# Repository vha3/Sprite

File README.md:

# Compressed Sprite

This board is schematically identical to the one in the master branch, but uses smaller surface-mount components to reduce the board footprint from 3.5x3.5 cm to 3x3 cm. The users' manual from the master branch applies to this board as well.

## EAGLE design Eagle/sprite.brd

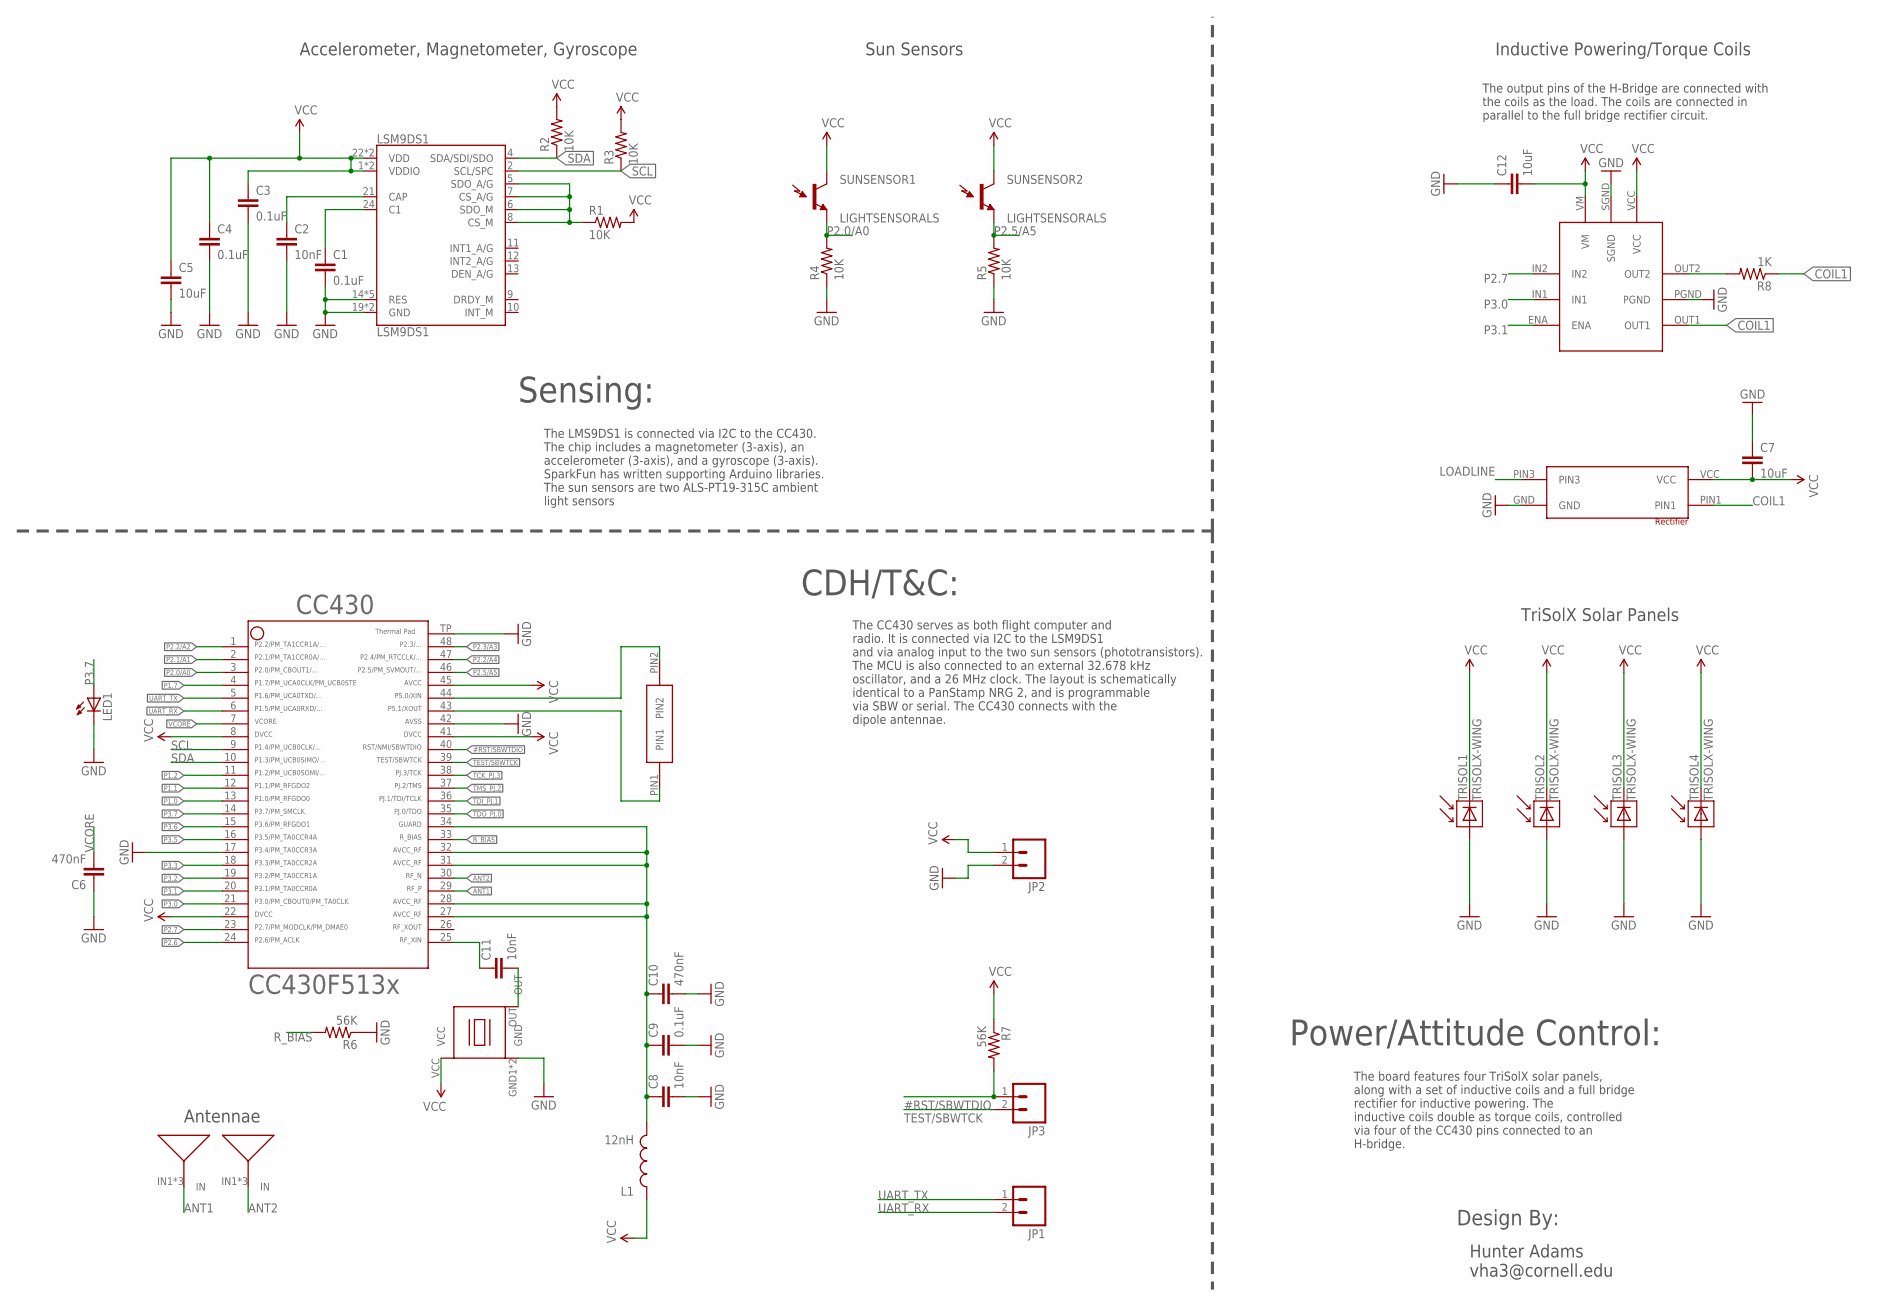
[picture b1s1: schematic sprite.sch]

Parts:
32KHZ: SPRITECRYSTALSPRITECRYSTAL; SPRITECRYSTAL
ANTENNA1, ANTENNA2: ANTENNA
C1, C3, C4, C9: 0.1uF; 0402-CAP
C2, C8, C11: 10nF; 0402-CAP
C5, C7, C12: 10uF; 0402-CAP
C6, C10: 470nF; 0402-CAP
CC430: CC430F513X---RGZ48; RGZ48
H-BRIDGE: LV8417CS
JP1, JP2, JP3: M02PTH; 1X02
L1: 12nH; C0402
LED1: LED0603; LED-0603
LSM9DS1: LSM9DS1; LGA24-8X4
R1, R2, R3, R4, R5: 10K; 0402-RES
R6, R7: 56K; 0402-RES
R8: 1K; 0402-RES
RECTIFIER: NSR1030QMUTAG
SUNSENSOR1, SUNSENSOR2: LIGHTSENSORALS; ALS-PT19
TRISOL1, TRISOL2, TRISOL3, TRISOL4: TRISOLX-WING; TRISOLX-T01
TXCO: TCXO_7Z; TXC_7Z

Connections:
#RST/SBWTDIO: CC430.40, JP3.1, R7.2
ANT1: ANTENNA1.IN1, ANTENNA1.IN2, ANTENNA1.IN3, CC430.29
ANT2: ANTENNA2.IN1, ANTENNA2.IN2, ANTENNA2.IN3, CC430.30
COIL1: H-BRIDGE.OUT1, R8.1, RECTIFIER.PIN1
GND: C1.2, C2.2, C3.2, C4.2, C5.2, C6.1, C7.1, C8.2, C9.2, C10.2, C12.1, CC430.17, CC430.42, CC430.TP (49), H-BRIDGE.PGND, H-BRIDGE.SGND, JP2.2, LED1.C, LSM9DS1.14 (RES), LSM9DS1.15 (RES), LSM9DS1.16 (RES), LSM9DS1.17 (RES), LSM9DS1.18 (RES), LSM9DS1.19 (GND), LSM9DS1.20 (GND), R4.1, R5.1, R6.1, RECTIFIER.GND, TRISOL1.P$3 (A), TRISOL2.P$3 (A), TRISOL3.P$3 (A), TRISOL4.P$3 (A), TXCO.GND1 (GND), TXCO.GND2 (GND)
GUARD: C8.1, C9.1, C10.1, CC430.27, CC430.28, CC430.31, CC430.32, CC430.34, L1.2
LOADLINE: H-BRIDGE.OUT2, R8.2, RECTIFIER.PIN3
unnamed: C1.1, LSM9DS1.24 (C1)
unnamed: C2.1, LSM9DS1.21 (CAP)
unnamed: LSM9DS1.5 (SDO_A/G), LSM9DS1.6 (SDO_M), LSM9DS1.7 (CS_A/G), LSM9DS1.8 (CS_M), R1.1
unnamed: C11.1, CC430.25
unnamed: C11.2, TXCO.OUT
unnamed: 32KHZ.PIN2, CC430.44
unnamed: 32KHZ.PIN1, CC430.43
P1.0: CC430.13
P1.1: CC430.12
P1.2: CC430.11
P1.7: CC430.4
P2.0/A0: CC430.3, R4.2, SUNSENSOR1.E (E1)
P2.1/A1: CC430.2
P2.2/A2: CC430.1
P2.2/A4: CC430.47
P2.3/A3: CC430.48
P2.5/A5: CC430.46, R5.2, SUNSENSOR2.E (E1)
P2.6: CC430.24
P2.7: CC430.23, H-BRIDGE.IN2
P3.0: CC430.21, H-BRIDGE.IN1
P3.1: CC430.20, H-BRIDGE.ENA
P3.2: CC430.19
P3.3: CC430.18
P3.5: CC430.16
P3.6: CC430.15
P3.7: CC430.14, LED1.A
R_BIAS: CC430.33, R6.2
SCL: CC430.9, LSM9DS1.2 (SCL/SPC), R3.1
SDA: CC430.10, LSM9DS1.4 (SDA/SDI/SDO), R2.1
TCK_PJ.3: CC430.38
TDI_PJ.1: CC430.36
TDO_PJ.0: CC430.35
TEST/SBWTCK: CC430.39, JP3.2
TMS_PJ.2: CC430.37
UART_RX: CC430.6, JP1.2
UART_TX: CC430.5, JP1.1
VCC: C3.1, C4.1, C5.1, C7.2, C12.2, CC430.8, CC430.22, CC430.41, CC430.45, H-BRIDGE.VCC, H-BRIDGE.VM, JP2.1, L1.1, LSM9DS1.1 (VDDIO), LSM9DS1.3 (VDDIO), LSM9DS1.22 (VDD), LSM9DS1.23 (VDD), R1.2, R2.2, R3.2, R7.1, RECTIFIER.VCC, SUNSENSOR1.C (C1), SUNSENSOR2.C (C1), TRISOL1.P$2 (C), TRISOL2.P$2 (C), TRISOL3.P$2 (C), TRISOL4.P$2 (C), TXCO.VCC
VCORE: C6.2, CC430.7

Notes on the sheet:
Accelerometer, Magnetometer, Gyroscope
Sun Sensors
The LMS9DS1 is connected via I2C to the CC430. The chip includes a magnetometer (3-axis), an accelerometer (3-axis), and a gyroscope (3-axis). SparkFun has written supporting Arduino libraries. The sun sensors are two ALS-PT19-315C ambient light sensors
Sensing:
CDH/T&C:
The CC430 serves as both flight computer and radio. It is connected via I2C to the LSM9DS1 and via analog input to the two sun sensors (phototransistors). The MCU is also connected to an external 32.678 kHz oscillator, and a 26 MHz clock. The layout is schematically identical to a PanStamp NRG 2, a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
Power/Attitude Control:
The board features four TriSolX solar panels, along with a set of inductive coils and a full bridge rectifier for inductive powering. The inductive coils double as torque coils, controlled via four of the CC430 pins connected to an H-bridge.
Antennae
TriSolX Solar Panels
Inductive Powering/Torque Coils
Hunter Adams vha3@cornell.edu
Design By:
The output pins of the H-Bridge are connected with the coils as the load. The coils are connected in parallel to the full bridge rectifier circuit.

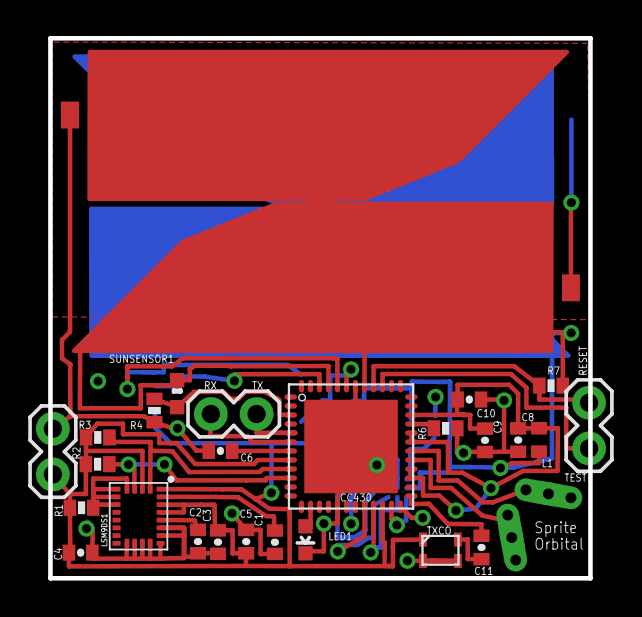
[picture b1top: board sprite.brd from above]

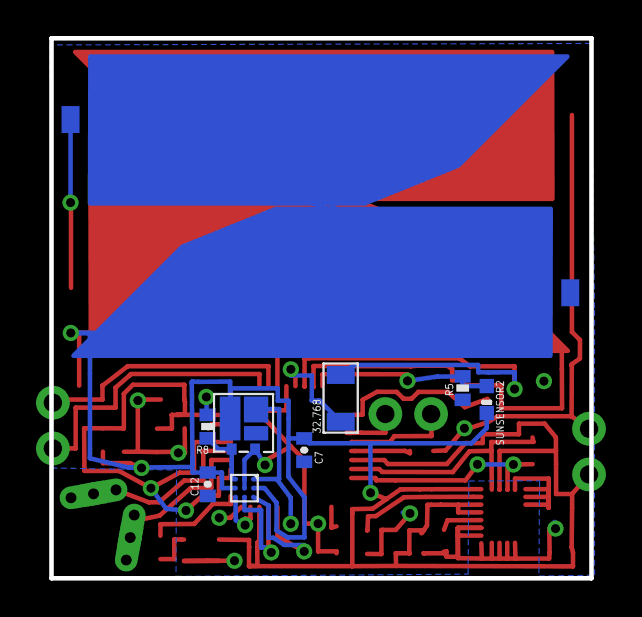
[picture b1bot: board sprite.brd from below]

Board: 4 copper layers, 30.0 x 30.0 mm, 39 parts (10 on the bottom side), 28 nets.

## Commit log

2016-05-01 board and schematic files
2016-05-01 swapped in tcxo
2016-05-03 added Gerbers, fixed DRC errors
2016-05-03 zipped Gerbers and image files
2016-05-13 added CPL document
2016-06-05 fixed reset line, added current-limiting resistor and bypass cap
2016-06-05 added identifying silkscreen
2016-06-06 spaced out resistor
2016-06-06 added demo scripts
2016-06-07 updated gerbers
2016-06-07 Delete Board.png
    outdated
2016-06-07 Delete EagleCAD.zip
    outdated
2016-06-07 Delete sprite_b.csv
    outdated
2016-06-17 cleaned up repo
2016-06-20 added panStamp sketches
2016-06-20 reorganized repo
2016-06-20 eliminated outdated files
2016-06-20 readme in demo folder
2016-06-20 added some explanation, linked panStamp
2016-06-21 added user manual
2016-06-22 added informational image
2016-06-22 updated informatinoal poster
2016-06-22 made informational poster an image file
2016-06-22 updated image files
2016-06-22 updated images
2016-06-22 updated user manual
2016-06-22 updated image
2016-07-13 updated manual
2016-07-28 Test commit for new branch
2016-07-28 Got rid of interface pins
2016-07-31 Resized, still needs spacers
2016-07-31 Diverted torque coils around IMU
2016-07-31 Added silkscreen component labels
2016-08-01 updated images, BOM, CPL
2016-09-25 Battery Sprite

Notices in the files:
parts and their libraries:
SparkFun-Sensors: Licensing: Creative Commons ShareAlike 4.0 International - https://creativecommons.org/licenses/by-sa/4.0
SparkFun: Licensing: CC v3.0 Share-Alike You are welcome to use this library for commercial purposes.
